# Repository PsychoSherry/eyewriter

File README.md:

# Eyewriter

A DIY, open-source remote eye tracking toolkit meant to enable artistic digital expression for artists and students with diverse needs. 

This repo contains all of the source files necessary to fabricate and program the electronics system, as well as fabricate an adjustable 3D-printable platform that can be clamped onto any laptop or set on a table.

#### This repo contains:
* 3D files = all of the OpenSCAD scripts (and rendered STLs) for all of the 3D-printable files.
* Arduino sketches = sketches that can be loaded onto the electronics platform.
* BOMs = bills of materials for all required parts for the project.
* Eagle files = design files for all of the electronics modules
* oF app = openFrameworks program to translate camera data into usable actions

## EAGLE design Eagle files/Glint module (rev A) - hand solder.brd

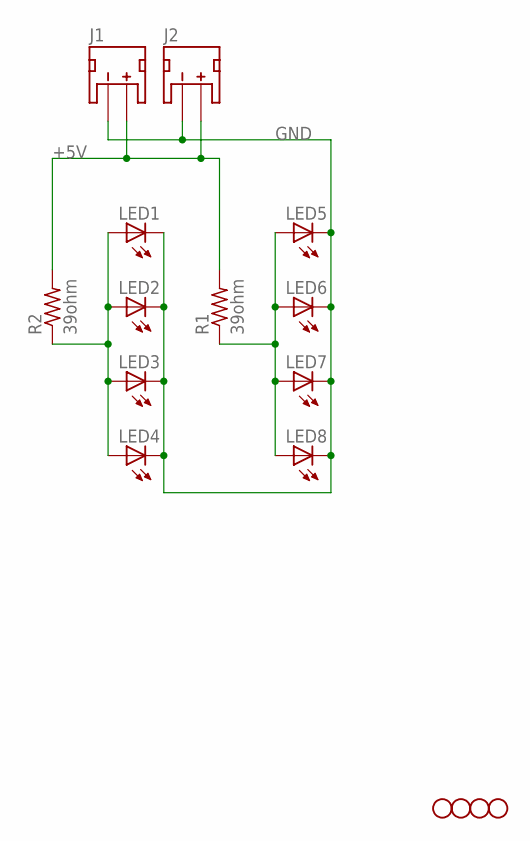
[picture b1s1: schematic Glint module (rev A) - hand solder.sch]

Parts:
J1, J2: JST_2MM_MALE; JST-2-SMD
LED1, LED2, LED3, LED4, LED5, LED6, LED7, LED8: LED5MM
R1, R2: 39ohm; 0309/10
STANDOFF1, STANDOFF2, STANDOFF3, STANDOFF4: STAND-OFF

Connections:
+5V: J1.2 (+), J2.2 (+), R1.2, R2.2
GND: J1.1 (-), J2.1 (-), LED1.K (C), LED2.K (C), LED3.K (C), LED4.K (C), LED5.K (C), LED6.K (C), LED7.K (C), LED8.K (C)
unnamed: LED1.A, LED2.A, LED3.A, LED4.A, R2.1
unnamed: LED5.A, LED6.A, LED7.A, LED8.A, R1.1

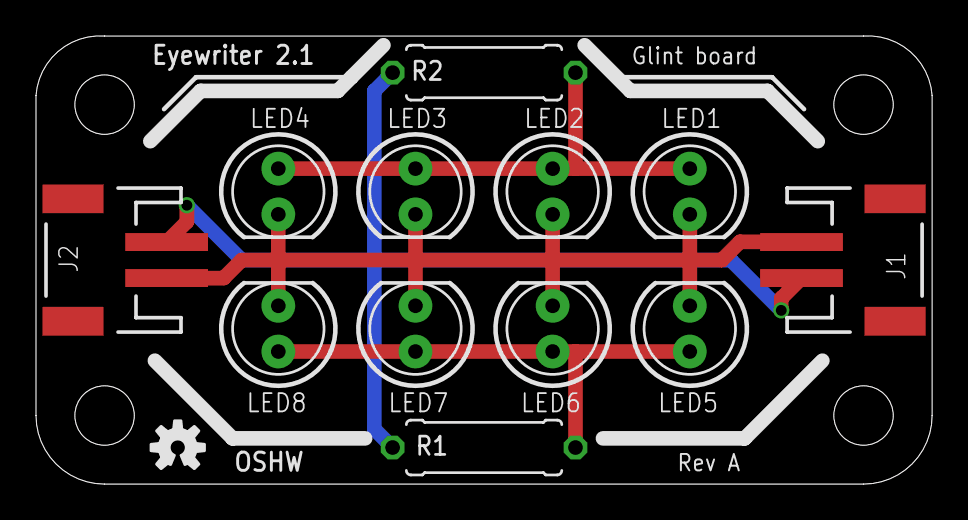
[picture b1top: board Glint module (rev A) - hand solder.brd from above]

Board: 2 copper layers, 49.8 x 24.9 mm, 17 parts (0 on the bottom side), 4 nets.

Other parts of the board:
U$1: OSHW-LOGO-S

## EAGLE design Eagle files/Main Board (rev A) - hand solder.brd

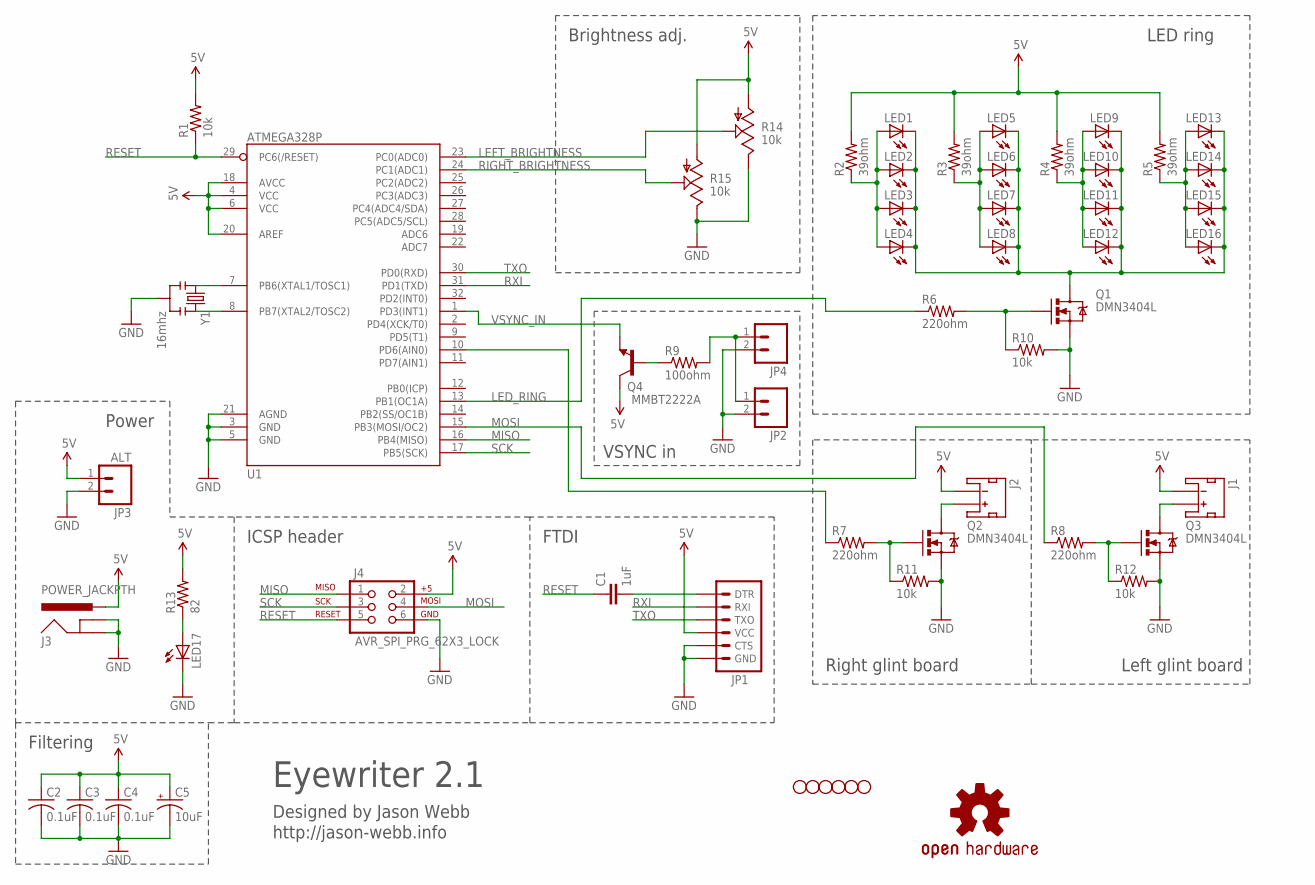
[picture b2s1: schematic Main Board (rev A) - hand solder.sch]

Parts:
C1: 1uF; 0805
C2, C3, C4: 0.1uF; C0805K
C5: 10uF; A/3216-18R
J1, J2: JST_2MM_MALE; JST-2-SMD
J3: POWER_JACKPTH; POWER_JACK_PTH
J4: AVR_SPI_PRG_62X3_LOCK; 2X3_LOCK
JP1: ARDUINO_SERIAL_PROGRAMLOCK; 1X06_LOCK
JP2, JP4: M02PTH; 1X02
JP3: ALT; 1X02
LED1, LED2, LED3, LED4, LED5, LED6, LED7, LED8, LED9, LED10, LED11, LED12, LED13, LED14, LED15, LED16: LED5MM
LED17: LEDCHIPLED_0805; CHIPLED_0805
LOGO1: OSHW-LOGOS; OSHW-LOGO-S
Q1, Q2, Q3: DMN3404L; SOT23-3
Q4: MMBT2222A; SOT23
R1, R10, R11, R12: 10k; 0805
R2, R3, R4, R5: 39ohm; 0309/10
R6, R7, R8: 220ohm; 0805
R9: 100ohm; 0805
R13: 82; 0805
R14, R15: 10k; ALPS_POT
STANDOFF1, STANDOFF2, STANDOFF3, STANDOFF4, STANDOFF5, STANDOFF6: STAND-OFF
U1: ATMEGA328P; TQFP32-08
Y1: 16mhz; RESONATOR-PTH

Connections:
5V: C2.1, C3.1, C4.1, C5.+, J1.1 (-), J2.1 (-), J3.PWR, J4.2, JP1.4 (VCC), JP3.1, Q4.3 (C), R1.2, R2.2, R3.2, R4.2, R5.2, R13.2, R14.P$3 (A), R15.P$3 (A), U1.4 (VCC), U1.6 (VCC), U1.18 (AVCC), U1.20 (AREF)
GLINT_RIGHT: R8.1, U1.15 (PB3(MOSI/OC2))
GND: C2.2, C3.2, C4.2, C5.-, J3.GND, J3.GNDBREAK, J4.6, JP1.5 (CTS), JP1.6 (GND), JP2.2, JP3.2, JP4.2, LED17.C, Q1.2 (S), Q2.2 (S), Q3.2 (S), R10.2, R11.2, R12.2, R14.P$1 (E), R15.P$1 (E), U1.3 (GND), U1.5 (GND), U1.21 (AGND), Y1.2
LED_RING: R6.1, U1.13 (PB1(OC1A))
LEFT_BRIGHTNESS: R14.P$2 (S), U1.23 (PC0(ADC0))
MISO: J4.1, U1.16 (PB4(MISO))
MOSI: J4.4, R7.1, U1.10 (PD6(AIN0))
unnamed: LED17.A, R13.1
unnamed: U1.7 (PB6(XTAL1/TOSC1)), Y1.1
unnamed: U1.8 (PB7(XTAL2/TOSC2)), Y1.3
unnamed: LED1.A, LED2.A, LED3.A, LED4.A, R2.1
unnamed: J2.2 (+), Q2.3 (D)
unnamed: LED5.A, LED6.A, LED7.A, LED8.A, R3.1
unnamed: Q1.1 (G), R6.2, R10.1
unnamed: LED9.A, LED10.A, LED11.A, LED12.A, R4.1
unnamed: Q2.1 (G), R7.2, R11.1
unnamed: LED13.A, LED14.A, LED15.A, LED16.A, R5.1
unnamed: J1.2 (+), Q3.3 (D)
unnamed: JP2.1, JP4.1, R9.2
unnamed: LED1.K (C), LED2.K (C), LED3.K (C), LED4.K (C), LED5.K (C), LED6.K (C), LED7.K (C), LED8.K (C), LED9.K (C), LED10.K (C), LED11.K (C), LED12.K (C), LED13.K (C), LED14.K (C), LED15.K (C), LED16.K (C), Q1.3 (D)
unnamed: Q3.1 (G), R8.2, R12.1
unnamed: Q4.1 (B), R9.1
unnamed: C1.2, JP1.1 (DTR)
RESET: C1.1, J4.5, R1.1, U1.29 (PC6(/RESET))
RIGHT_BRIGHTNESS: R15.P$2 (S), U1.24 (PC1(ADC1))
RXI: JP1.2 (RXI), U1.31 (PD1(TXD))
SCK: J4.3, U1.17 (PB5(SCK))
TXO: JP1.3 (TXO), U1.30 (PD0(RXD))
VSYNC_IN: Q4.2 (E), U1.1 (PD3(INT1))

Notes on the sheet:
ICSP header
FTDI
LED ring
Right glint board
Left glint board
Brightness adj.
VSYNC in
Power
Eyewriter 2.1
Designed by Jason Webb
http://jason-webb.info
Filtering

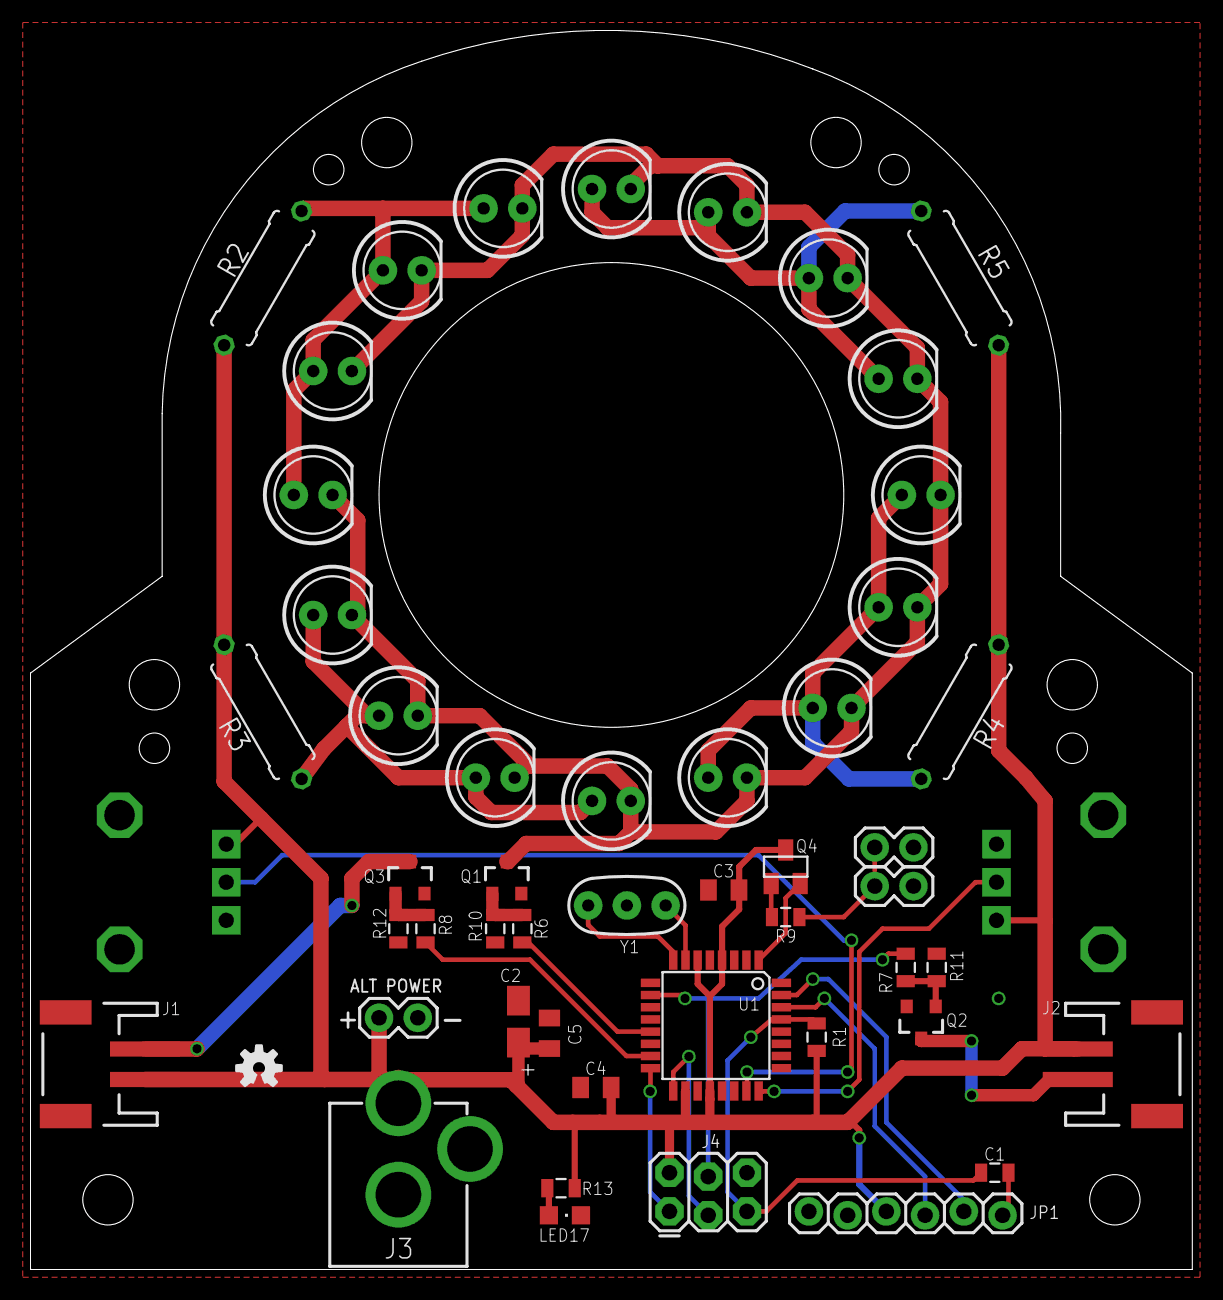
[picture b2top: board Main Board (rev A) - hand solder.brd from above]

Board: 2 copper layers, 76.2 x 81.2 mm, 58 parts (0 on the bottom side), 29 nets.

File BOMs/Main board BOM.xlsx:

ID | Value | Package | Qty | Cost | Total | Part number | Source
R1 | 10k | 0805 | 1 | 0.1 | 0.1 | P10KACT-ND | http://www.digikey.com/product-detail/en/ERJ-6GEYJ103V/P10KA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
R2-R5 | 39ohm | 1W power resistor | 4 | 0.34 | 1.36 | P39W-1BK-ND | http://www.digikey.com/product-detail/en/ERG-1SJ390/P39W-1BK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
R6-R8 | 220ohm | 0805 | 3 | 0.1 | 0.30000000000000004 | P220ACT-ND | http://www.digikey.com/product-detail/en/ERJ-6GEYJ221V/P220A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
R9 | 100ohm | 0805 | 1 | 0.1 | 0.1 | P100ACT-ND | http://www.digikey.com/product-detail/en/ERJ-6GEYJ101V/P100A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
R10-R12 | 10k | 0805 | 3 | 0.1 | 0.30000000000000004 | P10KACT-ND | http://www.digikey.com/product-detail/en/ERJ-6GEYJ103V/P10KA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
R13 | 89ohm | 0805 | 1 | 0.1 | 0.1 | P82ACT-ND | http://www.digikey.com/product-detail/en/ERJ-6GEYJ820V/P82AC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
R14-R15 | 10k | Panel mount pot | 2 | 1.05 | 2.1 | P3A1103-ND | http://www.digikey.com/product-detail/en/EVU-F3AF30B14/P3A11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
C1 | 1uF | 0805 | 1 | 0.1 | 0.1 | 445-3463-1-ND | http://www.digikey.com/product-detail/en/C2012Y5V1H105Z%2F0.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
C2-C4 | 0.1uF | 0805 | 3 | 0.1 | 0.30000000000000004 | 445-7534-1-ND | http://www.digikey.com/product-detail/en/C2012X7R1H104K085AA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
C5 | 10uF | 1206 | 1 | 0.44 | 0.44 | 493-4147-1-ND | http://www.digikey.com/product-detail/en/F931C106KAA/493-414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
Q1-Q3 | DMN3404L | SOT-23-3 | 3 | 0.45 | 1.35 | DMN3404LDICT-ND | http://www.digikey.com/product-detail/en/DMN3404L-7/DMN3404L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
Q4 | MMBT2222A | SOT-23-3 | 1 | 0.14000000000000001 | 0.14000000000000001 | MMBT2222A-FDICT-ND | http://www.digikey.com/product-detail/en/MMBT2222A-7-F/MMBT2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
U1 | ATMEGA328P | 32-TQFP | 1 | 3.05 | 3.05 | ATMEGA328P-AU-ND | http://www.digikey.com/product-detail/en/ATMEGA328P-AU/ATMEG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
Y1 | 16MHz | 3-SMD | 1 | 0.48 | 0.48 | 490-1198-1-ND | http://www.digikey.com/product-detail/en/CSTCE16M0V53-R0/490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
LED1-LED16 | 940nm IR | 5mm (T 1 3/4) | 16 | 0.36120000000000002 | 5.7792000000000003 | 751-1204-ND | http://www.digikey.com/product-detail/en/TSAL6200/751-1204-N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
LED17 | Green LED | 0805 | 1 | 0.08 | 0.08 | 475-1410-1-ND | http://www.digikey.com/product-detail/en/LG%20R971-KN-1-0-20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
J1-J2 | 2-pin JST female | SMD R/A | 2 | 0.56000000000000005 | 1.1200000000000001 | 455-1749-1-ND | http://www.digikey.com/product-detail/en/S2B-PH-SM4-TB(LF)(S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
 |  |  |  | Total | 17.199200000000001

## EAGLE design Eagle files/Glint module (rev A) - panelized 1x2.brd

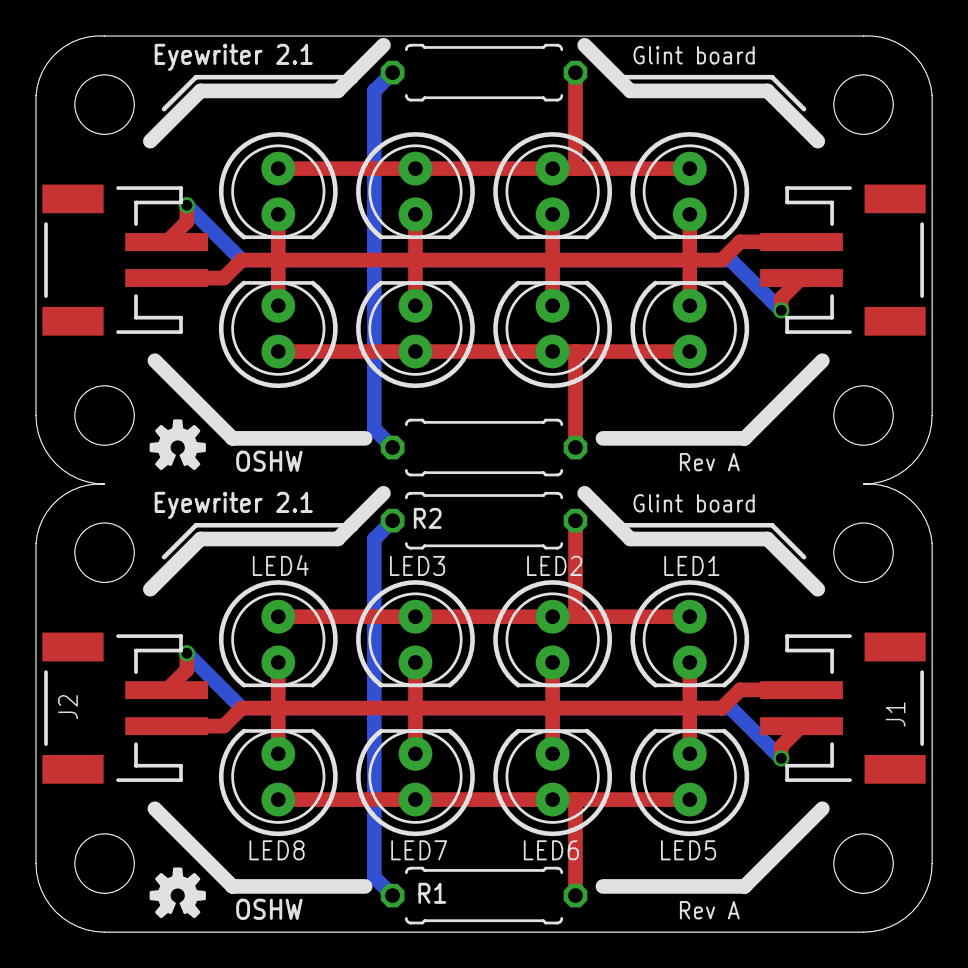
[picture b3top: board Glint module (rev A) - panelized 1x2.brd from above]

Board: 2 copper layers, 49.8 x 49.8 mm, 34 parts (0 on the bottom side), 8 nets.

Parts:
J1, J2, J3, J4: JST-2-SMD
LED1, LED2, LED3, LED4, LED5, LED6, LED7, LED8, LED9, LED10, LED11, LED12, LED13, LED14, LED15, LED16: LED5MM
R1, R2, R3, R4: 39ohm; 0309/10
STANDOFF1, STANDOFF2, STANDOFF3, STANDOFF4, STANDOFF5, STANDOFF6, STANDOFF7, STANDOFF8: STAND-OFF
U$1, U$2: OSHW-LOGO-S

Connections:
+5V: J1.2, J2.2, R1.2, R2.2
+5V1: J3.2, J4.2, R3.2, R4.2
GND: J1.1, J2.1, LED1.K, LED2.K, LED3.K, LED4.K, LED5.K, LED6.K, LED7.K, LED8.K
GND1: J3.1, J4.1, LED9.K, LED10.K, LED11.K, LED12.K, LED13.K, LED14.K, LED15.K, LED16.K
unnamed: LED1.A, LED2.A, LED3.A, LED4.A, R2.1
unnamed: LED9.A, LED10.A, LED11.A, LED12.A, R4.1
unnamed: LED5.A, LED6.A, LED7.A, LED8.A, R1.1
unnamed: LED13.A, LED14.A, LED15.A, LED16.A, R3.1

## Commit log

2013-04-02 Major first commit
2013-04-02 Removing old eyeWriterTracker folder
2013-05-01 Updated Eagle files, including Gerbers and custom library
2013-05-22 Updated Eagle files + BOMs
2013-05-22 Updated Eagle files
2013-05-29 Removing files
2013-12-04 Linux Issues I'm having

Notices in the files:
parts and their libraries:
SparkFun-LED: Licensing: CC v3.0 Share-Alike You are welcome to use this library for commercial purposes.
